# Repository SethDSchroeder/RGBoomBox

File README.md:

# RGBoomBox

The RGBBoomBox is a bluetooth speaker with BLINKENLIGHTS

**6/24 update** I'm reworking and completing this project now based around an Arduino MEGA board. Ideally, the first iteration will be designed as a shield for the mega which the daughter components plug into. After that, it will be revamped into a single board. All further updates to this project will be in the MEGA branch until it is semi-functional then I will merge it back into main.

**List of components used:**

* Bluetooth audio board: https://www.amazon.com/gp/product/B07W4PJ469/ref=ppx_yo_dt_b_search_asin_title?ie=UTF8&psc=1
* Audio amplifier: https://www.adafruit.com/product/1752
* RGB Matrix: https://www.adafruit.com/product/420
* Rotary encoder for volume: https://www.sparkfun.com/products/15141 and https://www.sparkfun.com/products/10597
* Matrix shield: https://www.adafruit.com/product/2601

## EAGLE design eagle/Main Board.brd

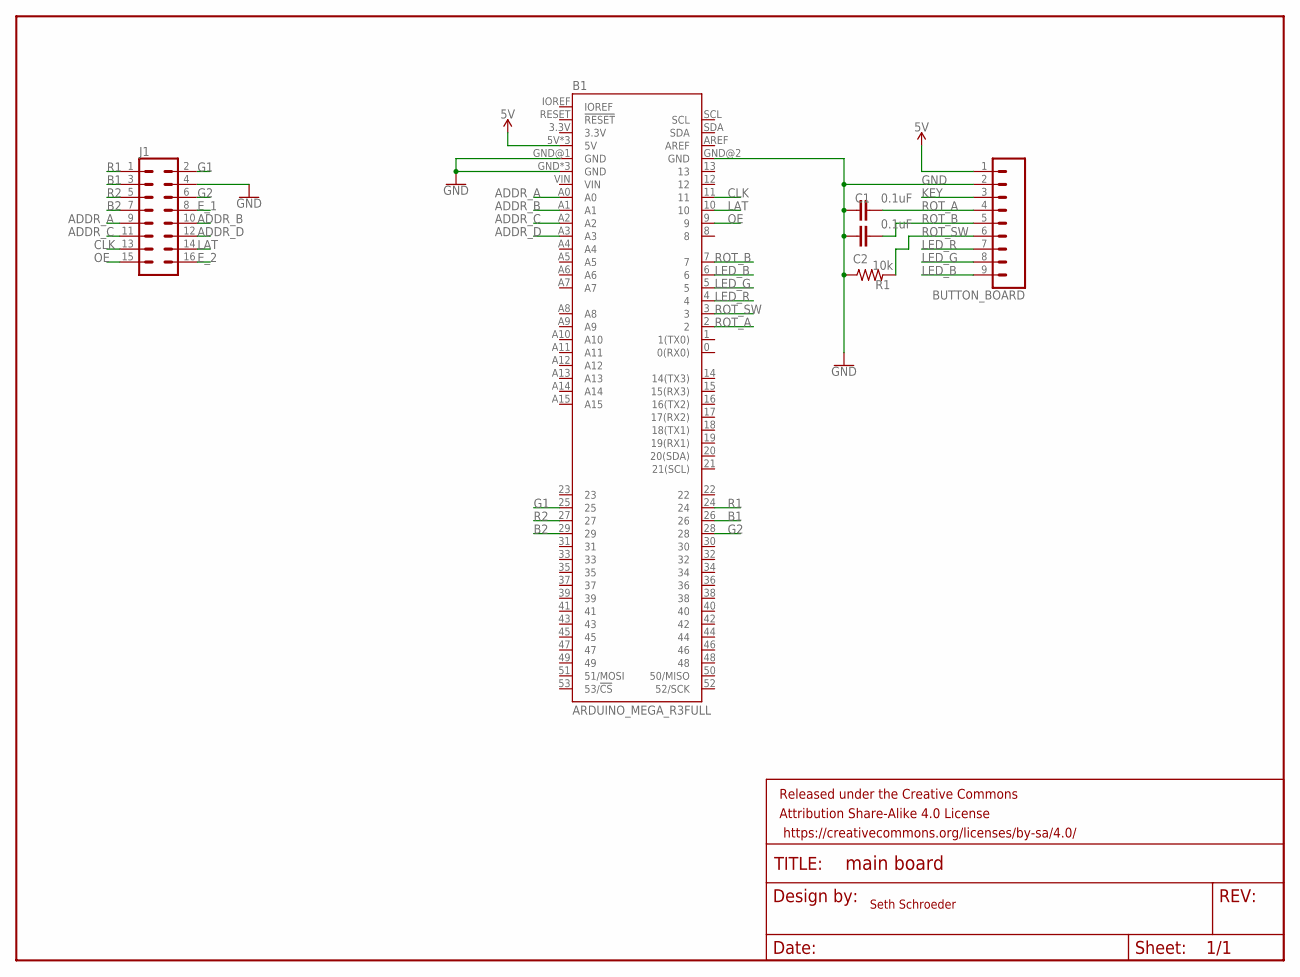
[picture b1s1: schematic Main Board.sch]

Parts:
B1: ARDUINO_MEGA_R3FULL; ARDUINO_MEGA_NO_SILK
BUTTON_BOARD: CONN_09; 1X09
C1, C2: 0.1uF; CAP-PTH-SMALL-KIT
FRAME1: FRAME-LETTER; CREATIVE_COMMONS
J1: CONN_08X2_SHROUD; 2X8-SHROUDED_LOCK
R1: 10k; AXIAL-0.3

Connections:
5V: B1.5V, B1.5V@1 (5V), B1.5V@2 (5V), BUTTON_BOARD.1
ADDR_A: B1.A0, J1.9
ADDR_B: B1.A1, J1.10
ADDR_C: B1.A2, J1.11
ADDR_D: B1.A3, J1.12
B1: B1.26, J1.3
B2: B1.29, J1.7
CLK: B1.11, J1.13
E_1: J1.8
E_2: J1.16
G1: B1.25, J1.2
G2: B1.28, J1.6
GND: B1.GND, B1.GND@1 (GND), B1.GND@2 (GND), B1.GND@3 (GND), B1.GND@4 (GND), BUTTON_BOARD.2, C1.1, C2.1, J1.4, R1.P$1 (1)
KEY: BUTTON_BOARD.3
LAT: B1.10, J1.14
LED_B: B1.6, BUTTON_BOARD.9
LED_G: B1.5, BUTTON_BOARD.8
LED_R: B1.4, BUTTON_BOARD.7
OE: B1.9, J1.15
R1: B1.24, J1.1
R2: B1.27, J1.5
ROT_A: B1.2, BUTTON_BOARD.4, C1.2
ROT_B: B1.7, BUTTON_BOARD.5, C2.2
ROT_SW: B1.3, BUTTON_BOARD.6, R1.P$2 (2)

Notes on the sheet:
Seth Schroeder

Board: 2 copper layers, 7 parts (0 on the bottom side), 21 nets, no tracks yet.

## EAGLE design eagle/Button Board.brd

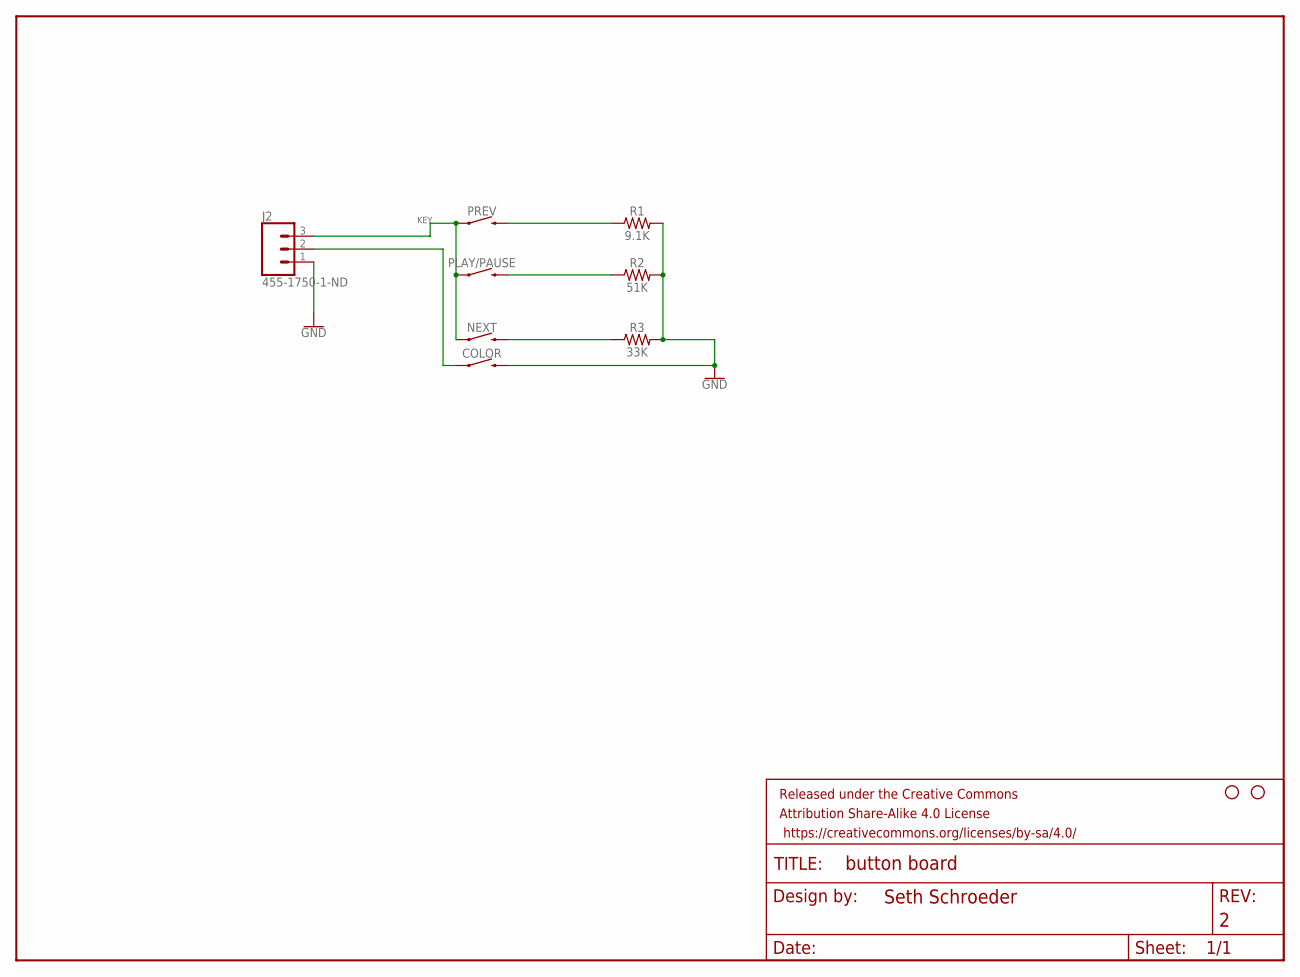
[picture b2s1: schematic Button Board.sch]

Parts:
COLOR: MOMENTARY-SWITCH-SPST-PTH-12MM; TACTILE_SWITCH_PTH_12MM
H1, H2: STAND-OFF
J2: 455-1750-1-ND; 1X03
ME: Seth; CREATIVE_COMMONS
NEXT: MOMENTARY-SWITCH-SPST-PTH-12MM; TACTILE_SWITCH_PTH_12MM
PLAY/PAUSE: MOMENTARY-SWITCH-SPST-PTH-12MM; TACTILE_SWITCH_PTH_12MM
PREV: MOMENTARY-SWITCH-SPST-PTH-12MM; TACTILE_SWITCH_PTH_12MM
R1: 9.1K; AXIAL-0.3
R2: 51K; AXIAL-0.3
R3: 33K; AXIAL-0.3

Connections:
GND: COLOR.3 (2), J2.1, R1.P$2 (2), R2.P$2 (2), R3.P$2 (2)
KEY: J2.3, NEXT.1, PLAY/PAUSE.1, PREV.1
unnamed: COLOR.1, J2.2
unnamed: PREV.3 (2), R1.P$1 (1)
unnamed: PLAY/PAUSE.3 (2), R2.P$1 (1)
unnamed: NEXT.3 (2), R3.P$1 (1)

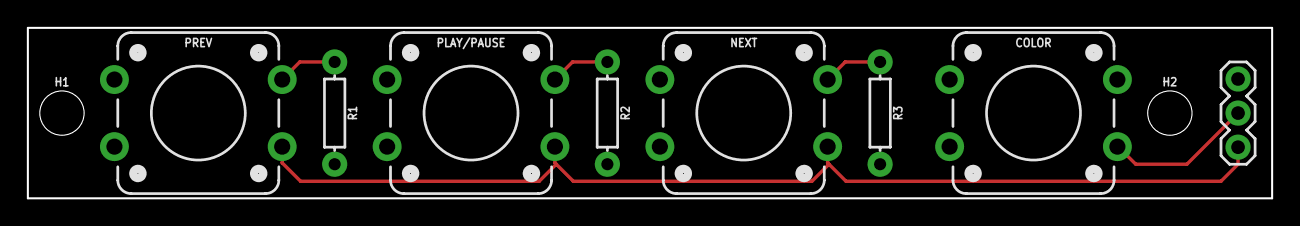
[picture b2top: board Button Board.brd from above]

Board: 2 copper layers, 92.7 x 12.7 mm, 11 parts (0 on the bottom side), 6 nets.

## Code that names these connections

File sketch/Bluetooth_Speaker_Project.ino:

#include <PinChangeInt.h>
#include <Wire.h>
#include <Adafruit_MCP23X08.h>
#include <arduinoFFT.h>
#include <SPI.h>
#include <RGBmatrixPanel.h>

//init audio amp
// 0x4B is the default i2c address
#define MAX9744_I2CADDR 0x4B

//#define ROT_SW A1         // rotary puhbutton
// Global variables that can be changed in interrupt routines
volatile int volume = 32;                     // current "position" of rotary encoder (increments CW)
volatile boolean rotary_change = false;      // will turn true if rotary_counter has changed
volatile boolean button_pressed = false;     // will turn true if the button has been pushed
volatile boolean button_released = false;    // will turn true if the button has been released (sets button_downtime)
volatile unsigned long button_downtime = 0L; // ms the button was pushed before release
static boolean button_down = false;
static unsigned long int button_down_start, button_down_time;
boolean muted = true; //Using this boole prevents us from having to infinitely write high or low to the pin if it doesn't need to be

//Init MCP23008
Adafruit_MCP23X08 mcp;

//Init GPIO controls
#define MUTE 13  //Digital 13
#define ROT_B 12 // rotary B
#define ROT_A 11 // rotary A

//These are the values for the bars
#define SAMPLES 64 //Must be a power of 2
#define xres 32    // Total number of  columns in the display, must be <= SAMPLES/2
#define yres 16    // Total number of  rows in the display

#define NUM_LEDS (xres * yres)

#define CLK 8 // USE THIS ON ARDUINO UNO, ADAFRUIT METRO M0, etc.
//#define CLK A4 // USE THIS ON METRO M4 (not M0)
//#define CLK 11 // USE THIS ON ARDUINO MEGA
#define OE 9
#define LAT 10
#define A A0
#define B A1
#define C A2

//Init the matrix panel
RGBmatrixPanel matrix(A, B, C, CLK, LAT, OE, false);

byte yvalue;
byte displaycolumn, displayvalue;
int peaks[xres];
byte state = HIGH;        // the current reading from the input pin
byte previousState = LOW; // the previous reading from the input pin
byte displaycolor = 0;

//Arrays for samplig
double vReal[SAMPLES];
double vImag[SAMPLES];
byte data_avgs[xres];
arduinoFFT FFT = arduinoFFT(); // FFT object

unsigned long lastDebounceTime = 0; // the last time the output pin was toggled
unsigned long debounceDelay = 100;  // the debounce time; increase if the output flickers

// EQ filter to attenuates bass and improves treble
// Useful on PC sound card which usually has many bass and poor high frequency
bool EQ_ON = true; // set to false to disable eq
byte eq[32] = {5, 10, 30, 70, 75, 80, 85, 95,
               100, 100, 100, 100, 100, 100, 100, 100,
               100, 100, 100, 100, 100, 100, 100, 100,
               115, 125, 140, 160, 185, 200, 225, 255};

void setup()
{

  //Initialize audio amplifer
  Serial.begin(9600);
  Serial.println("MAX9744 demo with volume modulated by rotary encoder.");
  Wire.begin();

  if (!setvolume(volume))
  {
    Serial.println("Failed to set volume, MAX9744 not found!");
    while (1)
      ;
  }

  //Init mcp
  /* if (!mcp.begin_I2C())
  {
    Serial.println("Cannot address mcp chip.");
    while (1)
      ;
  } */

  //Init matrix
  matrix.begin();
  ADCSRA = 0b11100101; // set ADC to free running mode and set pre-scalar to 32 (0xe5)
  ADMUX = 0b00000011;  // use pin A4 and internal voltage reference

  //Init GPIO
  //Rotary encoder
  pinMode(ROT_B, INPUT);
  digitalWrite(ROT_B, HIGH); // turn on weak pullup
  pinMode(ROT_A, INPUT);
  digitalWrite(ROT_A, HIGH); // turn on weak pullup
  //pinMode(ROT_SW, INPUT);
  //Interrupts for the rotary encoder
  //attachInterrupt(digitalPinToInterrupt(3), rotaryIRQ, CHANGE);
  PCintPort::attachInterrupt(ROT_A, &rotaryIRQ, CHANGE);
  //muting
  pinMode(MUTE, INPUT);
}


void rotaryIRQ()
{
  static unsigned char rotary_state = 0; // current and previous encoder states

  rotary_state <<= 2;                                               // remember previous state
  rotary_state |= (digitalRead(ROT_A) | (digitalRead(ROT_B) << 1)); // mask in current state
  rotary_state &= 0x0F;                                             // zero upper nybble

  Serial.println(rotary_state, HEX);

  if (rotary_state == 0x06) // from 10 to 01, increment counter. Also try 0x06 if unreliable
  {
    volume++;
    rotary_change = true;
  }
  else if (rotary_state == 0x0C) // from 00 to 11, decrement counter. Also try 0x0C if unreliable
  {
    volume--;
    rotary_change = true;
  }
}

boolean setvolume(int8_t v)
{
  Serial.print("Setting volume to ");
  Serial.println(v);
  Wire.beginTransmission(MAX9744_I2CADDR);
  Wire.write(v);
  if (Wire.endTransmission() == 0)
    return true;
  else
    return false;
}

void loop()
{
  if (rotary_change)
  {
    volume = constrain(volume, 0, 63);
    setvolume(volume);
    rotary_change = false;
  }
  if (!digitalRead(MUTE))
  { //If the hw board IS playing
    muted = false;
  }
  if (digitalRead(MUTE))
  { //If hw board is NOT playing
    muted = true;
  }

  // ++ Sampling
  for (int i = 0; i < SAMPLES; i++)
  {
    while (!(ADCSRA & 0x10))
      ;                    // wait for ADC to complete current conversion ie ADIF bit set
    ADCSRA = 0b11110101;   // clear ADIF bit so that ADC can do next operation (0xf5)
    int value = ADC - 512; // Read from ADC and subtract DC offset caused value
    vReal[i] = value / 8;  // Copy to bins after compressing
    vImag[i] = 0;
  }

  FFT.Windowing(vReal, SAMPLES, FFT_WIN_TYP_HAMMING, FFT_FORWARD);
  FFT.Compute(vReal, vImag, SAMPLES, FFT_FORWARD);
  FFT.ComplexToMagnitude(vReal, vImag, SAMPLES);

  // -- FFT
  // ++ re-arrange FFT result to match with no. of columns on display (xres)
  int step = (SAMPLES / 2) / xres;
  int c = 0;
  for (int i = 0; i < (SAMPLES / 2); i += step)
  { //This just loops through 32
    data_avgs[c] = 0;
    for (int k = 0; k < step; k++)
    {
      data_avgs[c] = data_avgs[c] + vReal[i + k];
    }
    data_avgs[c] = data_avgs[c] / step;
    c++;
  }

  // ++ send to display according measured value
  for (int i = 0; i < xres; i++)
  { //again looping through 32
    if (EQ_ON)
      data_avgs[i] = data_avgs[i] * (float)(eq[i]) / 100; //apply eq filter
    data_avgs[i] = constrain(data_avgs[i], 0, 50);        // set max & min values for buckets to 0-80
    data_avgs[i] = map(data_avgs[i], 0, 50, 0, yres);     // remap averaged values to yres 0-8
    yvalue = data_avgs[i];
    peaks[i] = peaks[i] - 1; // decay by one light
    if (yvalue > peaks[i])
      peaks[i] = yvalue; //save peak if > previuos peak
    yvalue = peaks[i];
    displaycolumn = i;
    displayvalue = yvalue;
    matrix.drawLine(displaycolumn, 0, displaycolumn, 15, matrix.Color333(0, 0, 0)); //Clear the column first before drawing it again
    matrix.drawLine(displaycolumn, 15 - displayvalue, displaycolumn, 15, matrix.Color333(random(0, 8), random(0, 8), random(0, 8))); //Draw the column
  }
}

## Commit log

2021-11-11 Added eagle files
2024-06-06 Added main board PDF
2024-06-22 added bluetooth board button schematic for reference
2024-06-24 Changed directory structure to satisfy arduino uno
2024-06-24 made edits to readme
2024-06-24 Made some edits to read me
2024-06-24 deleted duplicate file
2024-06-24 Deleted main board files, will redesign as mega shield when protoype is working.
2024-06-26 Created new main board file
2024-06-27 Attached pins on MEGA to LED matrix port, created online of MEGA shield
2024-06-29 Wired rotary encoder to arduino.

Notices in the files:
parts and their libraries:
SparkFun-Switches: Licensing: Creative Commons ShareAlike 4.0 International - https://creativecommons.org/licenses/by-sa/4.0
SparkFun-Aesthetics: Released under the Creative Commons Attribution Share-Alike 4.0 License
SparkFun-Aesthetics: https://creativecommons.org/licenses/by-sa/4.0
